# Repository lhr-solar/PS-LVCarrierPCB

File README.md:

# PS-LVCarrierPCB
One Big Beautiful Board

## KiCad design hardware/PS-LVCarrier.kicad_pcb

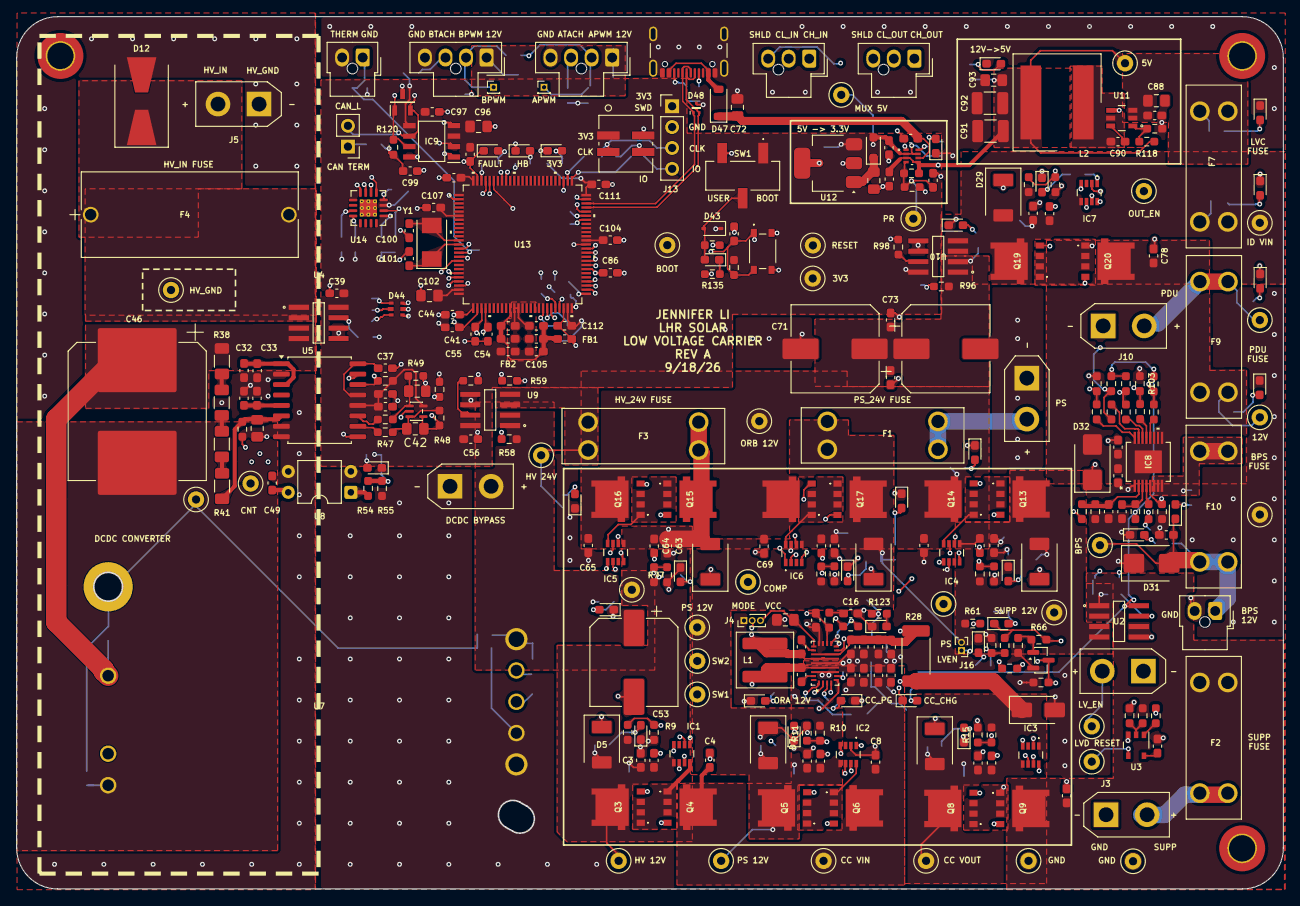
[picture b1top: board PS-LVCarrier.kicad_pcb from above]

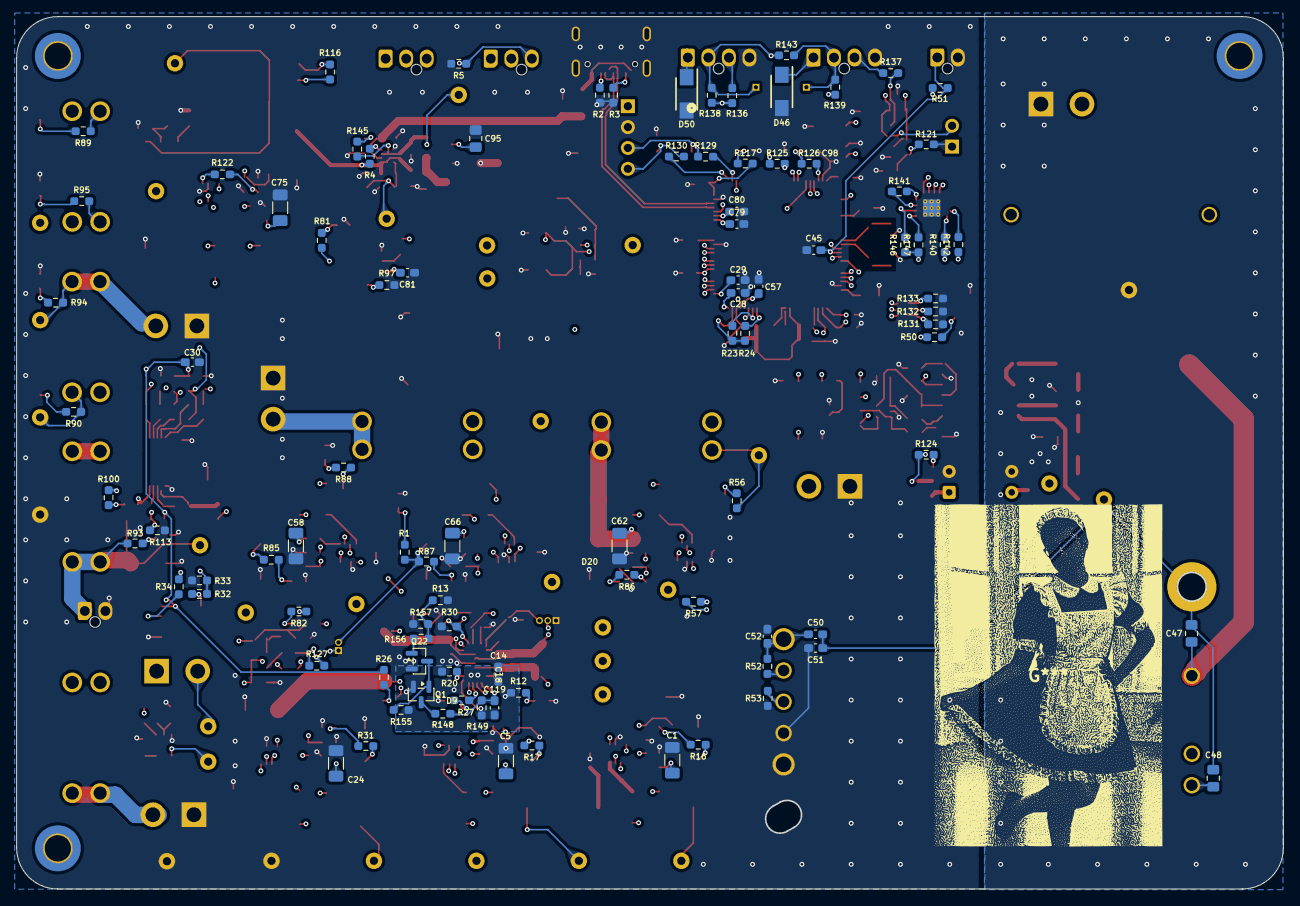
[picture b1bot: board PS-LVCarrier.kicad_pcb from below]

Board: 4 copper layers, 154.2 x 106.2 mm, 414 parts (95 on the bottom side), 209 nets.

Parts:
C1, C5, C24, C58, C62, C66, C75: 47u; C_1206_3216Metric_Pad1.33x1.80mm_HandSolder
C2, C4, C6, C8, C25, C27, C33, C35, C40, C59, C61, C63, C65, C67, C69, C76, C78, C85, C108, C110: 1u; C_0603_1608Metric_Pad1.08x0.95mm_HandSolder
C3, C7, C14, C18, C19, C26, C30, C39, C49, C56, C60, C64, C68, C77, C81, C97, C98, C99, C103, C104, C105, C106, C107, C109, C111, C112, C113, C114, C115, C116, C117, C119: 0.1u; C_0603_1608Metric_Pad1.08x0.95mm_HandSolder
C10, C11, C12, C13, C20, C21, C22, C23, C73, C74: 22u; C_0603_1608Metric_Pad1.08x0.95mm_HandSolder
C15, C31: 10n; C_0603_1608Metric_Pad1.08x0.95mm_HandSolder
C16: 4.7n; C_0603_1608Metric_Pad1.08x0.95mm_HandSolder
C17, C88: 4.7u; C_0805_2012Metric_Pad1.18x1.45mm_HandSolder
C28, C37, C45, C54, C57, C79, C83, C89, C90: 100n; C_0603_1608Metric_Pad1.08x0.95mm_HandSolder
C29, C41, C44, C55, C80, C86: 47n; C_0603_1608Metric_Pad1.08x0.95mm_HandSolder
C32, C34, C38, C84: 1n; C_0603_1608Metric_Pad1.08x0.95mm_HandSolder
C36: 1n; C_0805_2012Metric_Pad1.18x1.45mm_HandSolder
C42, C43: 1000p; C_0805_2012Metric_Pad1.18x1.45mm_HandSolder
C46: 100u; CP_Elec_16x22
C47, C48: 4700p; C_0805_2012Metric_Pad1.18x1.45mm_HandSolder
C50, C51: 0.022u; C_0603_1608Metric_Pad1.08x0.95mm_HandSolder
C52: 2.2u; C_0603_1608Metric_Pad1.08x0.95mm_HandSolder
C53: 680u; CP_Elec_10x10.5
C70, C71: 1000u; CP_Elec_10x12.5
C72, C94, C95, C96, C102: 10u; C_0805_2012Metric_Pad1.18x1.45mm_HandSolder
C82: 470n; C_0603_1608Metric_Pad1.08x0.95mm_HandSolder
C87: 2.2n; C_0603_1608Metric_Pad1.08x0.95mm_HandSolder
C91, C92: 22u; C_1210_3225Metric_Pad1.33x2.70mm_HandSolder
C93: 3.3u; C_0805_2012Metric_Pad1.18x1.45mm_HandSolder
C100, C101: 26p; C_0603_1608Metric_Pad1.08x0.95mm_HandSolder
D1: PS_LED; LED_0603_1608Metric_Pad1.05x0.95mm_HandSolder
D2: ORA_OUT_LED; LED_0603_1608Metric_Pad1.05x0.95mm_HandSolder
D3: D_Zener; D_SMA
D4, D6, D10, D17, D19, D21, D28: ORB_IN; LED_0603_1608Metric_Pad1.05x0.95mm_HandSolder
D5, D7, D11, D18, D20, D22, D29: SMBJ33D; SMBJ15DM3
D8, D9, D30, D45: LED; LED_0603_1608Metric_Pad1.05x0.95mm_HandSolder
D12: SMLJ150A; D_SMB-SMC_Universal_Handsoldering
D13, D14: HV24V_LED; LED_0603_1608Metric_Pad1.05x0.95mm_HandSolder
D15: DIODE_VOUT_LED; LED_0603_1608Metric_Pad1.05x0.95mm_HandSolder
D16: DISABLE_LED; LED_0603_1608Metric_Pad1.05x0.95mm_HandSolder
D23, D24: 12V_IN; LED_0603_1608Metric_Pad1.05x0.95mm_HandSolder
D25: HSS_IN; LED_0603_1608Metric_Pad1.05x0.95mm_HandSolder
D26: BPS_IN_LED; LED_0603_1608Metric_Pad1.05x0.95mm_HandSolder
D27: PDU_IN_LED; LED_0603_1608Metric_Pad1.05x0.95mm_HandSolder
D31, D32: D_TVS; D_SMB
D33, D49: 5V_LED; LED_0603_1608Metric_Pad1.05x0.95mm_HandSolder
D34: 3V3_LED; LED_0603_1608Metric_Pad1.05x0.95mm_HandSolder
D35: SBA130CH-AU_R1_000A1; D_SOD-323_HandSoldering
D36: CDSOT23-T24CAN
D37, D38: CHARGE_EN; LED_0603_1608Metric_Pad1.05x0.95mm_HandSolder
D39: DCDC_EN; LED_0603_1608Metric_Pad1.05x0.95mm_HandSolder
D40: HB_LED; LED_0603_1608Metric_Pad1.05x0.95mm_HandSolder
D41: FAULT_LED; LED_0603_1608Metric_Pad1.05x0.95mm_HandSolder
D42: LV_EN; LED_0603_1608Metric_Pad1.05x0.95mm_HandSolder
D43: TVS; D_SOD-323
D44: RGB_LED
D46, D50: VSSAF522-M3/H; SODFL5026X125N
D47: D_Schottky; D_SOD-123
D48: TPD2EUSB30DRTR
F1, F2, F3, F7, F9: TBD; Fuse-3557-2
F4: HV; HV-Fuse
F10: 5A; Fuse-3557-2
FB1, FB2: FerriteBead; C_0603_1608Metric_Pad1.08x0.95mm_HandSolder
H1, H2, H3: MountingHole; MountingHole_3.2mm_M3_DIN965_Pad_TopBottom
IC1, IC2, IC3, IC4, IC5, IC6, IC7: AP74502HQTA8-7; AP74502HQTA87
IC8: TPS2HCS08AQPWPRQ1
IC9: TCAN3413DR
J1: PS; AMASS_XT30UPB-M_1x02_P5.0mm_Vertical
J2: LV_ENABLE; AMASS_XT30UPB-M_1x02_P5.0mm_Vertical
J3: SUPP; AMASS_XT30UPB-M_1x02_P5.0mm_Vertical
J4: PWM/PFM; PinHeader_1x03_P1.00mm_Vertical
J5, J6: HV_IN; AMASS_XT30UPB-M_1x02_P5.0mm_Vertical
J8: HV_THERM; Molex_Nano-Fit_105309-xx02_1x02_P2.50mm_Vertical
J9: BPS_12V; Molex_Nano-Fit_105309-xx02_1x02_P2.50mm_Vertical
J10: PDU_12V; AMASS_XT30UPB-M_1x02_P5.0mm_Vertical
J11: CAN_IN; Molex_Nano-Fit_105309-xx03_1x03_P2.50mm_Vertical
J12: SWD_Header; SWD_Conn
J13: SWD; PinHeader_1x04_P2.54mm_Vertical
J14: FAN2; Molex_Nano-Fit_105309-xx04_1x04_P2.50mm_Vertical
J15: FAN1; Molex_Nano-Fit_105309-xx04_1x04_P2.50mm_Vertical
J16: in the off chance no supp pwr; PinHeader_1x02_P1.00mm_Vertical
J17: USB_C_Receptacle_USB2.0_16P; USB_C_Receptacle_GCT_USB4105-xx-A_16P_TopMnt_Horizontal
J18: CAN_OUT; Molex_Nano-Fit_105309-xx03_1x03_P2.50mm_Vertical
JP1: TRM; PinHeader_1x02_P2.54mm_Vertical
L1: 6.8u; L_Coilcraft_XAL6020-XXX
L2: 8.2u; 74439369082
Q1: BSS84; SOT-23
Q3, Q4, Q5, Q6, Q8, Q9, Q13, Q14, Q15, Q16, Q17, Q18, Q19, Q20: NVMFWS1D7N04XMT1G; NVMFWS3D0P04M8LT1G
Q10: IRLML0030; SOT-23
Q22: 2N7002; SOT-23
R1, R4, R9, R11, R12, R15, R16, R17, R31, R32, R42, R46, R47, R48, R49, R51, R56, R57, R58, R76, R78, R80, R81, R84, R85, R86, R87, R88, R89, R90, R92, R93, R95, R96, R102, R103, R106, R107, R108, R111, R112, R113, R128, R134, R136, R137, R138, R139, R140, R146, R147: 10k; R_0603_1608Metric_Pad0.98x0.95mm_HandSolder
R2, R3: 5.1k; R_0603_1608Metric_Pad0.98x0.95mm_HandSolder
R5, R52, R53, R143: 0; R_0603_1608Metric_Pad0.98x0.95mm_HandSolder
R8, R10, R14, R75, R77, R79, R91: 118k; R_0603_1608Metric_Pad0.98x0.95mm_HandSolder
R13, R23, R24, R29, R36, R55, R67, R118, R155, R157: 100k; R_0603_1608Metric_Pad0.98x0.95mm_HandSolder
R20: 49.9k; R_0603_1608Metric_Pad0.98x0.95mm_HandSolder
R25: 30k; R_0603_1608Metric_Pad0.98x0.95mm_HandSolder
R26, R27, R116, R117, R122, R123, R124, R125, R126, R127, R145: 1.3k; R_0603_1608Metric_Pad0.98x0.95mm_HandSolder
R28: 25m; R_2512_6332Metric_Pad1.40x3.35mm_HandSolder
R30: 8.66k; R_0603_1608Metric_Pad0.98x0.95mm_HandSolder
R33, R59, R66, R97, R131, R132, R133, R135, R156: 1k; R_0603_1608Metric_Pad0.98x0.95mm_HandSolder
R34, R45, R50, R60, R72, R98, R100, R110, R114: 4.7k; R_0603_1608Metric_Pad0.98x0.95mm_HandSolder
R35, R148: 200k; R_0603_1608Metric_Pad0.98x0.95mm_HandSolder
R37: 470k; R_0603_1608Metric_Pad0.98x0.95mm_HandSolder
R38, R39, R40, R41: 402k; R_1206_3216Metric_Pad1.30x1.75mm_HandSolder
R44, R61, R144: 47k; R_0603_1608Metric_Pad0.98x0.95mm_HandSolder
R54: 330; R_0603_1608Metric_Pad0.98x0.95mm_HandSolder
R68, R94, R142: 22k; R_0603_1608Metric_Pad0.98x0.95mm_HandSolder
R71: 16k; R_0603_1608Metric_Pad0.98x0.95mm_HandSolder
R82: 4.3k; R_0603_1608Metric_Pad0.98x0.95mm_HandSolder
R83, R141: 33k; R_0603_1608Metric_Pad0.98x0.95mm_HandSolder
R99, R104, R105, R129, R130: 22; R_0603_1608Metric_Pad0.98x0.95mm_HandSolder
R101: 10; R_0603_1608Metric_Pad0.98x0.95mm_HandSolder
R109: 220; R_0603_1608Metric_Pad0.98x0.95mm_HandSolder
R115: 470; R_0603_1608Metric_Pad0.98x0.95mm_HandSolder
R119: 19.1k; R_0603_1608Metric_Pad0.98x0.95mm_HandSolder
R120, R121: 60; R_0603_1608Metric_Pad0.98x0.95mm_HandSolder
R149: 26.1k; R_0603_1608Metric_Pad0.98x0.95mm_HandSolder
Reset1: Reset; TL3365AF180QG
SW1: SW_SPDT; BootSW
TP2: ORA_OUT_TP; TestPoint_Loop_D2.50mm_Drill1.0mm_LowProfile
TP3, TP4, TP9, TP30, TP31, TP32, TP39: DIODE_VIN; TestPoint_Loop_D2.50mm_Drill1.0mm_LowProfile
TP6: COMP; TestPoint_Loop_D2.50mm_Drill1.0mm_LowProfile
TP7: SW1; TestPoint_Loop_D2.50mm_Drill1.0mm_LowProfile
TP8: SW2; TestPoint_Loop_D2.50mm_Drill1.0mm_LowProfile
TP12: LVD_RESET; TestPoint_Loop_D2.50mm_Drill1.0mm_LowProfile
TP13: HV_GND; TestPoint_Loop_D2.50mm_Drill1.0mm_LowProfile
TP14, TP15, TP16: LV_GND; TestPoint_Loop_D2.50mm_Drill1.0mm_LowProfile
TP19: CNT; TestPoint_Loop_D2.50mm_Drill1.0mm_LowProfile
TP20: HV_24V_OUT; TestPoint_Loop_D2.50mm_Drill1.0mm_LowProfile
TP21: Earf; TestPoint_Loop_D2.50mm_Drill1.0mm_LowProfile
TP25: LV_EN_TP; TestPoint_Loop_D2.50mm_Drill1.0mm_LowProfile
TP26: SUPP_DIODE_EN; TestPoint_Loop_D2.50mm_Drill1.0mm_LowProfile
TP29: DIODE_VOUT; TestPoint_Loop_D2.50mm_Drill1.0mm_LowProfile
TP33: BOOT; TestPoint_Loop_D2.50mm_Drill1.0mm_LowProfile
TP34: RESET; TestPoint_Loop_D2.50mm_Drill1.0mm_LowProfile
TP35: OUTPUT_EN; TestPoint_Loop_D2.50mm_Drill1.0mm_LowProfile
TP36: PR1; TestPoint_Loop_D2.50mm_Drill1.0mm_LowProfile
TP37: BPS_IN_TP; TestPoint_Loop_D2.50mm_Drill1.0mm_LowProfile
TP38: PDU_IN_TP; TestPoint_Loop_D2.50mm_Drill1.0mm_LowProfile
TP42: HSS_VBB; TestPoint_Loop_D2.50mm_Drill1.0mm_LowProfile
TP43: Buck_5V; TestPoint_Loop_D2.50mm_Drill1.0mm_LowProfile
TP44: 3V3; TestPoint_Loop_D2.50mm_Drill1.0mm_LowProfile
TP45: MUX_5V; TestPoint_Loop_D2.50mm_Drill1.0mm_LowProfile
TP51: FAN_A_PWM; PinHeader_1x01_P1.00mm_Vertical
TP52: FAN_B_PWM; PinHeader_1x01_P1.00mm_Vertical
U1: TPS552872RYQR; TPS552872
U2, U9, U10: TMCS1107A2UQDR; TMCS1107A3BQDR
U3: TPS3840DL30DBVR; TPS3840DL33DBVR
U4: TMCS1107A3BQDR
U5: AMC3330; SOIC-16W_7.5x10.3mm_P1.27mm
U6: TLV6001DCK; SOT-353_SC-70-5
U7: CN150B110-12; lvc_dcdc
U8: LTV-817; DIP-4_W7.62mm
U11: LMR51635XDDCR; DDC0006A-MFG
U12: MCP1826S; SOT-223-3_TabPin2
U13: STM32G473VETx; 100PinMCU
U14: EMC2305-x-AP; Texas_RGV0016A_VQFN-16-1EP_4x4mm_P0.65mm_EP2.1x2.1mm_Therma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
U15: TPS2117DRLR
Y1: Crystal; Crystal_SMD_Abracon_ABM3-2Pin_5.0x3.2mm

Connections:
+3V3: C30.2, C38.1, C39.2, C40.1, C56.2, C81.2, C95.2, C96.1, C97.1, C98.1, C102.1, C104.1, C107.1, C109.1, C111.1, C112.1, FB2.1, IC9.3 (VCC), IC9.5 (SHDNV_IO), J12.1, J13.1, R23.1, R24.1, R26.1, R44.1, R51.1, R101.1, R102.1, R110.1, R111.2, R117.1, R128.2, R136.2, R137.2, R138.1, R139.1, R140.1, R141.1, R142.1, R146.1, R147.1, SW1.1 (A), TP44.1 (1_1), U2.8 (VS), U4.8 (VS), U5.12 (VDD), U6.5 (V+), U9.8 (VS), U10.8 (VS), U12.3 (VO), U13.6 (VBAT), U13.24 (VDD), U13.49 (VDD), U13.64 (VDD), U13.75 (VDD), U13.100 (VDD), U14.3 (VDD)
+12V: D46.1 (K), D50.1 (K), J14.1, J15.1
/CAN/CAN_RX: IC9.4 (RXD), U13.92 (PB5)
/CAN/CAN_TX: IC9.1 (TXD), U13.93 (PB6)
/CAN_H: D36.1 (CAN_H), IC9.7 (CANH), J11.1 (CAN_H), J18.1 (CAN_H), R120.1
/CAN_L: D36.2 (CAN_L), IC9.6 (CANL), J11.2 (CAN_L), J18.2 (CAN_L), JP1.2 (B)
/CHARGE_EN: R13.1, R123.1, R156.1, R157.2, U13.45 (PE14)
/CHG_CC: D8.1 (K), R23.2, U1.4 (*CC), U13.44 (PE13)
/CHG_PG: R24.2, R27.1, U1.3 (PG), U13.43 (PE12)
/DI_MODE: R108.1, R113.2, U13.58 (PD11)
/Fans/ADDR_SEL: R141.2, U14.4 (ADDR_SEL)
/Fans/FAN_ALERT: R140.2, U13.2 (PE3), U14.12 (~ALERT)
/Fans/FAN_A_PWM: J15.2, R138.2, R143.1, TP51.1 (1_1), U14.5 (PWM1)
/Fans/FAN_A_TACH: J15.3, R136.1, U14.6 (TACH1)
/Fans/FAN_B_PWM: J14.2, R139.2, R143.2, TP52.1 (1_1), U14.7 (PWM2)
/Fans/FAN_B_TACH: J14.3, R137.1, U14.8 (TACH2)
/Fans/FAN_CLK: R142.2, U14.11 (CLK)
/Fans/I2C_SCL: R146.2, U13.78 (PA15), U14.2 (SMCLK)
/Fans/I2C_SDA: R147.2, U13.96 (PB9), U14.1 (SMDATA)
/HSS_FLT_WK: R110.2, R112.2, U13.61 (PD14)
/HSS_MOSI: R99.1, R103.2, U13.54 (PB15)
/HSS_SCLK: R105.1, R106.2, U13.52 (PB13)
/HSS_SNS: C86.2, R114.2, U13.57 (PD10)
/HSS_SPI_CS: R102.2, R104.1, U13.62 (PD15)
/HV Input/HV -> 12V/CNT: C49.1, TP19.1 (1_1), U7.2 (CNT), U8.4
/HV Input/HV -> 12V/HV_24V_OUT: F3.1, R56.1, TP20.1 (1_1), U9.3 (IN-), U9.4 (IN-)
/HV Input/HV -> 12V/HV_IN: C46.1, C47.1, R38.1, U4.3 (IN-), U4.4 (IN-), U7.1 (IN+)
/HV Input/HV -> 12V/OUT+: C50.1, C52.1, C53.1, J6.2, R52.2, R57.1, R58.1, U7.9 (OUT+), U9.1 (IN+), U9.2 (IN+)
/HV Input/HV Input/DCDC_OUT: C32.1, C33.1, U5.1 (DCDC_OUT), U5.3 (HLDO_IN)
/HV Input/HV Input/HLDO_OUT: C34.1, C35.1, U5.5 (HLDO_OUT)
/HV Input/HV Input/HV_ISNS: R50.1, U4.7 (VOUT)
/HV Input/HV Input/HV_VSNS: C42.1, R45.1, R48.2, U6.4
/HV Input/HV Input/HV_VSNS+: R46.1, U5.11 (OUTP)
/HV Input/HV Input/HV_VSNS-: R47.2, U5.10 (OUTN)
/HV Input/HV Input/IN+: C36.2, R41.2, R42.1, U5.6 (INP)
/HV Input/HV Input/LDO_OUT: C37.1, U5.13 (LDO_OUT), U5.16 (DCDC_IN)
/HV Input/HV_12V_FUSED: C1.1, C2.1, C3.1, C62.1, C63.1, C64.1, D5.2 (A), D20.2 (A), F3.2, IC1.5 (VIN), IC5.5 (VIN), Q3.5, Q3.6, Q3.7, Q3.8, Q3.9, Q15.5, Q15.6, Q15.7, Q15.8, Q15.9, R8.1, R16.1, R77.1, R86.1, TP3.1 (1_1), TP31.1 (1_1)
/HV_DCDC_EN: R54.2, R55.1, R124.1, U13.17 (PC2)
/HV_DCDC_TEMP: C45.2, J8.1, R51.2, U13.15 (PC0)
/HV_IN_I: C44.1, R50.2, U13.26 (PA4)
/HV_IN_V: C41.1, R45.2, U13.27 (PA5)
/HV_IN_VFAULT: R44.2, U5.14 (DIAG), U13.16 (PC1)
/HV_OUT_I: C55.1, R60.2, U13.28 (PA6)
/HV_OUT_V: C54.1, R58.2, R59.1, U13.29 (PA7)
/LIMP_HOME: IC8.5 (LHI), R107.2, U13.59 (PD12)
/LVD_RESET: TP12.1 (1_1), U3.4 (MR_N), U13.47 (PB10)
/LV_EN_3V3: C57.1, R83.2, R84.2, R127.1, U13.46 (PE15)
/LV_I: C80.1, R98.2, U13.70 (PA9)
/LV_V: C79.1, R96.2, R97.1, U13.69 (PA8)
/MCU/FAULT: R126.1, U13.98 (PE1)
/MCU/HEARTBEAT: R125.1, U13.97 (PE0)
/MCU/STM32G473VETx/BOOT0: R134.1, TP33.1 (1_1), U13.95 (PB8-BOOT0)
/MCU/STM32G473VETx/GNDA: C103.2, C105.2, C108.2, C110.2, C113.2, FB1.1, U13.35 (VSSA)
/MCU/STM32G473VETx/NRST: C106.1, R128.1, Reset1.1, TP34.1 (1_1), U13.14 (PG10-NRST)
/MCU/STM32G473VETx/PA0: D44.5, U13.20 (PA0-GPIO_BLUE)
/MCU/STM32G473VETx/PA1: D44.3, U13.21 (PA1-GPIO_RED)
/MCU/STM32G473VETx/PA2: D44.1, U13.22 (PA2-GPIO_GREEN)
/MCU/STM32G473VETx/SWCLK: R129.1, U13.77 (PA14)
/MCU/STM32G473VETx/SWDIO: R130.1, U13.76 (PA13)
/MCU/STM32G473VETx/VDDA: C103.1, C105.1, C108.1, C110.1, C113.1, FB2.2, U13.36 (VREF+), U13.37 (VDDA)
/MISO: R109.1, R111.1, U13.53 (PB14)
/Main Diode ORs/12V_FUSED: C61.1, C65.1, C69.1, C70.1, C71.1, C73.1, C74.1, Q14.5, Q14.6, Q14.7, Q14.8, Q14.9, Q16.5, Q16.6, Q16.7, Q16.8, Q16.9, Q18.5, Q18.6, Q18.7, Q18.8, Q18.9, R81.1, R88.1, R96.1, TP29.1 (1_1), U10.1 (IN+), U10.2 (IN+)
/Main Diode ORs/HV_OVLO: IC5.7 (OVLO), R77.2, R78.1
/Main Diode ORs/Ideal Diode1/GATE: IC4.6 (GATE), Q13.4, Q14.4
/Main Diode ORs/Ideal Diode1/SRC: IC4.8 (SRC), Q13.1, Q13.2, Q13.3, Q14.1, Q14.2, Q14.3
/Main Diode ORs/Ideal Diode2/GATE: IC5.6 (GATE), Q15.4, Q16.4
/Main Diode ORs/Ideal Diode2/SRC: IC5.8 (SRC), Q15.1, Q15.2, Q15.3, Q16.1, Q16.2, Q16.3
/Main Diode ORs/Ideal Diode3/GATE: IC6.6 (GATE), Q17.4, Q18.4
/Main Diode ORs/Ideal Diode3/SRC: IC6.8 (SRC), Q17.1, Q17.2, Q17.3, Q18.1, Q18.2, Q18.3
/Main Diode ORs/PS_12V_FUSED: C5.1, C6.1, C7.1, C66.1, C67.1, C68.1, D7.2 (A), D22.2 (A), F1.2, IC2.5 (VIN), IC6.5 (VIN), J16.2, Q5.5, Q5.6, Q5.7, Q5.8, Q5.9, Q17.5, Q17.6, Q17.7, Q17.8, Q17.9, R1.1, R10.1, R17.1, R79.1, R87.1, TP4.1 (1_1), TP32.1 (1_1)
/Main Diode ORs/PS_OVLO: IC6.7 (OVLO), R79.2, R80.1
/Main Diode ORs/SUPP_12V_FUSED: C58.1, C59.1, C60.1, D18.2 (A), IC4.5 (VIN), Q13.5, Q13.6, Q13.7, Q13.8, Q13.9, R61.1, R75.1, R82.1, R85.1, TP30.1 (1_1), U2.3 (IN-), U2.4 (IN-)
/Main Diode ORs/SUPP_OVLO: IC4.7 (OVLO), R75.2, R76.1
/OUTPUT_EN: IC7.1 (EN/UVLO), R122.1, TP35.1 (1_1), U13.71 (PA10)
/Ouput/12V_OUT: C78.1, C84.1, C85.1, D32.2 (A2), F9.1, IC8.17 (VBB), Q20.5, Q20.6, Q20.7, Q20.8, Q20.9, R90.1, TP42.1 (1_1)
/Ouput/BPS_FUSED: C83.2, D30.1 (K), D31.2 (A2), F10.2, J9.1, R93.1, TP37.1 (1_1)
/Ouput/HSS/HSS_FLT_WAKE: IC8.12 (~FLT_/_~WAKE_SIG), R112.1
/Ouput/HSS/HSS_SPI_CS: IC8.15 (NCS), R104.2
/Ouput/HSS/MOSI: IC8.13 (SDI), R99.2
/Ouput/HSS/SCLK: IC8.16 (SCLK), R105.2
/Ouput/HSS/SNS: C87.2, IC8.2 (SNS), R114.1, R115.1
/Ouput/HSS/VDD: C82.1, IC8.3 (VDD), R101.2
/Ouput/HSS/VOUT1: F10.1, IC8.6 (VOUT1_1), IC8.7 (VOUT1_2), IC8.8 (VOUT1_3), R100.1
/Ouput/Ideal Diode/DIODE_VIN: C75.1, C76.1, C77.1, D29.2 (A), F7.2, IC7.5 (VIN), Q19.5, Q19.6, Q19.7, Q19.8, Q19.9, R91.1, R95.1, TP39.1 (1_1), U10.3 (IN-), U10.4 (IN-)
/Ouput/Ideal Diode/GATE: IC7.6 (GATE), Q19.4, Q20.4
/Ouput/Ideal Diode/OVLO: IC7.7 (OVLO), R91.2, R92.1
/Ouput/Ideal Diode/SRC: IC7.8 (SRC), Q19.1, Q19.2, Q19.3, Q20.1, Q20.2, Q20.3
/Ouput/LVC_12V_FUSED: C88.1, C89.1, F7.1, R89.1, U11.2 (EN), U11.3 (VIN)
/Ouput/PDU_FUSED: F9.2, J10.2, R94.1, TP38.1 (1_1)
/Power + Data/5V -> 3.3V LDO/Vin: C117.1, D35.2 (A), R145.1, TP45.1 (1_1), U15.2 (VOUT), U15.7 (VOUT__1)
/Power + Data/12V -> 5V Buck Converter/CB: C90.1, U11.6 (CB)
/Power + Data/12V -> 5V Buck Converter/FB: R118.2, R119.1, U11.1 (FB)
/Power + Data/12V -> 5V Buck Converter/SW: C90.2, L2.1, U11.5 (SW)
/Power + Data/12V -> 5V Buck Converter/V_out_5V: C91.1, C92.1, C93.1, C114.1, L2.2, R4.1, R71.1, R116.1, R118.1, TP43.1 (1_1), U15.3 (VIN1), U15.5 (MODE)
/Power + Data/Power Mux/PR1: C116.1, R71.2, R72.1, TP36.1 (1_1), U15.4 (PR1)
/Power + Data/USB/CC1: J17.A5 (CC1), R2.2
/Power + Data/USB/CC2: J17.B5 (CC2), R3.2
/Power + Data/USB/VBUS_IN: D47.2 (A), J17.A4 (VBUS), J17.A9 (VBUS), J17.B4 (VBUS), J17.B9 (VBUS)
/Power + Data/USB_5V: C72.2, C115.1, D47.1 (K), U15.6 (VIN2)
/SHIELD: J11.3 (SHIELD), J18.3 (SHIELD), R5.1
/SUPP_I: C29.1, R34.2, U13.51 (PB12)
/SUPP_V: C28.1, R32.2, R33.1, U13.50 (PB11)
/Supp Input/CC Buck/BOOT1: C18.1, U1.20 (BOOT1)
/Supp Input/CC Buck/BOOT2: C19.1, U1.19 (BOOT2)
/Supp Input/CC Buck/CC_VIN: C4.1, C8.1, C10.1, C11.1, C12.1, C13.1, C14.1, Q1.2 (S), Q4.5, Q4.6, Q4.7, Q4.8, Q4.9, Q6.5, Q6.6, Q6.7, Q6.8, Q6.9, R12.1, R155.1, TP2.1 (1_1), U1.7 (VIN)
/Supp Input/CC Buck/CC_VOUT: C24.1, C25.1, C26.1, D3.1 (K), D11.2 (A), IC3.1 (EN/UVLO), IC3.5 (VIN), Q8.5, Q8.6, Q8.7, Q8.8, Q8.9, R14.1, R28.1, R29.1, R31.1, TP9.1 (1_1), U1.13 (ISN)
/Supp Input/CC Buck/COMP: C15.1, R25.1, TP6.1 (1_1), U1.15 (COMP)
/Supp Input/CC Buck/EN/UVLO: C119.1, R148.2, R149.1, U1.1 (EN/UVLO)
/Supp Input/CC Buck/FB: R29.2, R30.1, U1.14 (FB)
/Supp Input/CC Buck/FSW: R20.1, U1.6 (FSW)
/Supp Input/CC Buck/MODE: J4.2, U1.2 (MODE)
/Supp Input/CC Buck/SW1: C18.2, L1.1, TP7.1 (1_1), U1.8 (SW1)
/Supp Input/CC Buck/SW2: C19.2, L1.2, TP8.1 (1_1), U1.10 (SW2)
/Supp Input/CC Buck/VCC: C17.1, J4.3, U1.18 (VCC)
/Supp Input/CC Buck/VOUT: C20.1, C21.1, C22.1, C23.1, R28.2, U1.11 (VOUT), U1.12 (ISP)
/Supp Input/CC_OVLO: IC3.7 (OVLO), R14.2, R15.1
/Supp Input/HV_OVLO: IC1.7 (OVLO), R8.2, R9.1
/Supp Input/Ideal Diode1/GATE: IC2.6 (GATE), Q5.4, Q6.4
/Supp Input/Ideal Diode1/SRC: IC2.8 (SRC), Q5.1, Q5.2, Q5.3, Q6.1, Q6.2, Q6.3
/Supp Input/Ideal Diode3/GATE: IC1.6 (GATE), Q3.4, Q4.4
/Supp Input/Ideal Diode3/SRC: IC1.8 (SRC), Q3.1, Q3.2, Q3.3, Q4.1, Q4.2, Q4.3
/Supp Input/Ideal Diode4/GATE: IC3.6 (GATE), Q8.4, Q9.4
/Supp Input/Ideal Diode4/SRC: IC3.8 (SRC), Q8.1, Q8.2, Q8.3, Q9.1, Q9.2, Q9.3
/Supp Input/LV_ENABLE: D16.1 (K), J2.2, R66.1, R83.1, TP25.1 (1_1)
/Supp Input/PS_OVLO: IC2.7 (OVLO), R10.2, R11.1
/Supp Input/SUPP_FUSED: C27.1, F2.2, Q9.5, Q9.6, Q9.7, Q9.8, Q9.9, R32.1, R35.1, U2.1 (IN+), U2.2 (IN+)
/USB_D+: D48.1 (D+), J17.A6 (D+), J17.B6 (D+), U13.73 (PA12)
/USB_D-: D48.2 (D-), J17.A7 (D-), J17.B7 (D-), U13.72 (PA11)
DIODE_EN: IC1.1 (EN/UVLO), IC2.1 (EN/UVLO), IC4.1 (EN/UVLO), IC5.1 (EN/UVLO), IC6.1 (EN/UVLO), Q10.3 (D), R37.1, R61.2, R68.1, R144.2, TP26.1 (1_1)
Earth: C47.2, C48.1, C50.2, C51.1, TP21.1 (1_1), U7.10 (PLATE)
HV_GND: C32.2, C33.2, C34.2, C35.2, C36.1, C49.2, D12.2 (A2), J5.1, R42.2, TP13.1 (1_1), U5.2 (DCDC_HGND), U5.7 (INN), U5.8 (HGND), U8.3
LV_GND: C1.2, C2.2, C4.2, C5.2, C6.2, C8.2, C10.2, C11.2, C12.2, C13.2, C14.2, C15.2, C16.2, C17.2, C20.2, C21.2, C22.2, C23.2, C24.2, C25.2, C27.2, C28.2, C29.2, C30.1, C31.2, C37.2, C38.2, C39.1, C40.2, C41.2, C43.2, C44.2, C45.1, C51.2, C52.2, C53.2, C54.2, C55.2, C56.1, C57.2, C58.2, C59.2, C61.2, C62.2, C63.2, C65.2, C66.2, C67.2, C69.2, C70.2, C71.2, C72.1, C73.2, C74.2, C75.2, C76.2, C78.2, C79.2, C80.2, C81.1, C82.2, C83.1, C84.2, C85.2, C86.1, C87.1, C88.2, C89.2, C91.2, C92.2, C93.2, C94.1, C95.1, C96.2, C97.2, C98.2, C99.1, C100.1, C101.1, C102.2, C104.2, C106.2, C107.2, C109.2, C111.2, C112.2, C114.2, C115.2, C116.2, C117.2, C119.2, D1.1 (K), D2.1 (K), D3.2 (A), D4.1 (K), D5.1 (K), D6.1 (K), D7.1 (K), D9.1 (K), D10.1 (K), D11.1 (K), D13.1 (K), D14.1 (K), D15.1 (K), D17.1 (K), D18.1 (K), D19.1 (K), D20.1 (K), D21.1 (K), D22.1 (K), D23.1 (K), D24.1 (K), D25.1 (K), D26.1 (K), D27.1 (K), D28.1 (K), D29.1 (K), D31.1 (A1), D32.1 (A1), D33.1 (K), D34.1 (K), D36.3 (GND), D37.1 (K), D38.1 (K), D39.1 (K), D40.1 (K), D41.1 (K), D42.1 (K), D43.1 (A1), D46.2 (A), D48.3 (GND), D49.1 (K), D50.2 (A), FB1.2, IC1.2 (GND), IC2.2 (GND), IC3.2 (GND), IC4.2 (GND), IC5.2 (GND), IC6.2 (GND), IC7.2 (GND), IC8.1 (GND), IC9.2 (GND), IC9.8 (STB), J1.1, J3.1, J4.1, J6.1, J8.2, J9.2, J10.1, J12.2, J13.2, J14.4, J15.4, J17.A1 (GND), J17.A12 (GND), J17.B1 (GND), J17.B12 (GND), J17.S1 (SHIELD), J17.S2 (Shield), J17.S3 (Shield), J17.S4 (Shield), Q10.2 (S), Q22.2 (S), R2.1, R3.1, R5.2, R9.2, R11.2, R13.2, R15.2, R20.2, R30.2, R33.2, R36.2, R49.1, R53.1, R55.2, R59.2, R67.2, R68.2, R72.2, R76.2, R78.2, R80.2, R84.1, R92.2, R97.2, R103.1, R106.1, R107.1, R113.1, R115.2, R119.2, R131.2, R132.2, R133.2, R135.2, R149.2, R157.1, Reset1.2, SW1.3 (C), TP14.1 (1_1), TP15.1 (1_1), TP16.1 (1_1), U1.5 (DITH/SYNC), U1.9 (PGND), U1.17 (AGND), U2.5 (GND), U2.6 (NC), U3.3 (GND), U4.5 (GND), U4.6 (NC), U5.9 (GND), U5.15 (DCDC_GND), U6.2 (V-), U7.5 (OUT-), U7.6 (SENSE-), U8.2, U9.5 (GND), U9.6 (NC), U10.5 (GND), U10.6 (NC), U11.4 (GND), U12.2 (GND), U13.23 (VSS), U13.48 (VSS), U13.63 (VSS), U13.74 (VSS), U13.99 (VSS), U14.17 (GND), U15.1 (GND)
unnamed: C16.1, R25.2
unnamed: C99.2, R120.2, R121.1
unnamed: D1.2 (A), R1.2
unnamed: D2.2 (A), R12.2
unnamed: D4.2 (A), R16.2
unnamed: D6.2 (A), R17.2
unnamed: D8.2 (A), R26.2
unnamed: D9.2 (A), R27.2
unnamed: D10.2 (A), R31.2
unnamed: D12.1 (A1), F4.1, J5.2
unnamed: D13.2 (A), R56.2
unnamed: D14.2 (A), R57.2
unnamed: D15.2 (A), R81.2
unnamed: D16.2 (A), R82.2
unnamed: D17.2 (A), R85.2
unnamed: D19.2 (A), R86.2
unnamed: D21.2 (A), R87.2
unnamed: D23.2 (A), R88.2
unnamed: D24.2 (A), R89.2
unnamed: D25.2 (A), R90.2
unnamed: D26.2 (A), R93.2
unnamed: D27.2 (A), R94.2
unnamed: D28.2 (A), R95.2
unnamed: D30.2 (A), R100.2
unnamed: D33.2 (A), R116.2
unnamed: D34.2 (A), R117.2
unnamed: C94.2, D35.1 (K), U12.1 (VI)
unnamed: D37.2 (A), R122.2
unnamed: D38.2 (A), R123.2
unnamed: D39.2 (A), R124.2
unnamed: D40.2 (A), R125.2
unnamed: D41.2 (A), R126.2
unnamed: D42.2 (A), R127.2
unnamed: D43.2 (A2), D45.2 (A), R134.2, SW1.2 (B)
unnamed: D44.2, R131.1
unnamed: D44.4, R132.1
unnamed: D44.6, R133.1
unnamed: D45.1 (K), R135.1
unnamed: D49.2 (A), R145.2
unnamed: F4.2, U4.1 (IN+), U4.2 (IN+)
unnamed: C3.2, IC1.4 (VCP)
unnamed: C7.2, IC2.4 (VCP)
unnamed: C26.2, IC3.4 (VCP)
unnamed: C60.2, IC4.4 (VCP)
unnamed: C64.2, IC5.4 (VCP)
unnamed: C68.2, IC6.4 (VCP)
unnamed: C77.2, IC7.4 (VCP)
unnamed: IC8.4 (DI), R108.2
unnamed: IC8.14 (SDO), R109.2
unnamed: F1.1, J1.2
unnamed: F2.1, J3.2
unnamed: J12.3, J13.3, R129.2
unnamed: J12.4, J13.4, R130.2
unnamed: J16.1, R144.1
unnamed: JP1.1 (A), R121.2
unnamed: Q1.3 (D), R148.1
unnamed: Q1.1 (G), Q22.3 (D), R155.2
unnamed: Q10.1 (G), R66.2, R67.1
unnamed: Q22.1 (G), R156.2
unnamed: R38.2, R39.1
unnamed: R39.2, R40.1
unnamed: R40.2, R41.1
unnamed: R54.1, U8.1
unnamed: R34.1, U2.7 (VOUT)
unnamed: C31.1, U3.5 (CT)
unnamed: R37.2, U3.1 (RESET_N)
unnamed: R35.2, R36.1, U3.2 (VDD)
unnamed: C43.1, R46.2, R49.2, U6.1 (+)
unnamed: C42.2, R47.1, R48.1, U6.3 (-)
unnamed: C46.2, C48.2, U7.4 (IN-)
unnamed: R52.1, U7.8 (SENSE+)
unnamed: R53.2, U7.7 (TRM)
unnamed: R60.1, U9.7 (VOUT)
unnamed: R98.1, U10.7 (VOUT)
unnamed: C100.2, U13.12 (PF0-OSC_IN), Y1.2
unnamed: C101.2, U13.13 (PF1-OSC_OUT), Y1.1
unnamed: R4.2, U15.8 (ST)

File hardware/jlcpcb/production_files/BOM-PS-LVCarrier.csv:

Comment,Designator,Footprint,LCSC,Quantity
0.022u,"C50,C51",C_0603_1608Metric_Pad1.08x0.95mm_HandSolder,C1697,2
0.1u,"C103,C104,C105,C106,C107,C109,C111,C112,C113,C114,C115,C116,C117,C119,C14,C18,C19,C26,C3,C30,C39,C49,C56,C60,C64,C68,C7,C77,C81,C97,C98,C99",C_0603_1608Metric_Pad1.08x0.95mm_HandSolder,C14663,32
1.3k,"R116,R117,R122,R123,R124,R125,R126,R127,R145,R26,R27",R_0603_1608Metric_Pad0.98x0.95mm_HandSolder,C22767,11
10,R101,R_0603_1608Metric_Pad0.98x0.95mm_HandSolder,C313648,1
1000p,"C42,C43",C_0805_2012Metric_Pad1.18x1.45mm_HandSolder,C1791,2
1000u,"C70,C71",CP_Elec_10x12.5,C22387800,2
100k,"R118,R13,R155,R157,R23,R24,R29,R36,R55,R67",R_0603_1608Metric_Pad0.98x0.95mm_HandSolder,C25803,10
100n,"C28,C37,C45,C54,C57,C79,C83,C89,C90",C_0603_1608Metric_Pad1.08x0.95mm_HandSolder,C14663,9
100u,C46,CP_Elec_16x22,C487536,1
10k,"R1,R102,R103,R106,R107,R108,R11,R111,R112,R113,R12,R128,R134,R136,R137,R138,R139,R140,R146,R147,R15,R16,R17,R31,R32,R4,R42,R46,R47,R48,R49,R51,R56,R57,R58,R76,R78,R80,R81,R84,R85,R86,R87,R88,R89,R9,R90,R92,R93,R95,R96",R_0603_1608Metric_Pad0.98x0.95mm_HandSolder,C25804,51
10u,"C102,C72,C94,C95,C96",C_0805_2012Metric_Pad1.18x1.45mm_HandSolder,C440198,5
118k,"R10,R14,R75,R77,R79,R8,R91",R_0603_1608Metric_Pad0.98x0.95mm_HandSolder,C25806,7
12V_IN,"D23,D24",LED_0603_1608Metric_Pad1.05x0.95mm_HandSolder,C7371904,2
16k,R71,R_0603_1608Metric_Pad0.98x0.95mm_HandSolder,C137788,1
19.1k,R119,R_0603_1608Metric_Pad0.98x0.95mm_HandSolder,C844132,1
1k,"R131,R132,R133,R135,R156,R33,R59,R66,R97",R_0603_1608Metric_Pad0.98x0.95mm_HandSolder,C21190,9
1n,C84,C_0603_1608Metric_Pad1.08x0.95mm_HandSolder,C100040,1
1n,"C32,C34,C38",C_0603_1608Metric_Pad1.08x0.95mm_HandSolder,C1588,3
1n,C36,C_0805_2012Metric_Pad1.18x1.45mm_HandSolder,C62774,1
1u,"C108,C110,C2,C25,C27,C33,C35,C4,C40,C59,C6,C61,C63,C65,C67,C69,C76,C78,C8,C85",C_0603_1608Metric_Pad1.08x0.95mm_HandSolder,C15849,20
2.2n,C87,C_0603_1608Metric_Pad1.08x0.95mm_HandSolder,C1604,1
2.2u,C52,C_0603_1608Metric_Pad1.08x0.95mm_HandSolder,C57895,1
200k,"R148,R35",R_0603_1608Metric_Pad0.98x0.95mm_HandSolder,C25811,2
22,"R104,R105,R129,R130,R99",R_0603_1608Metric_Pad0.98x0.95mm_HandSolder,C2930077,5
220,R109,R_0603_1608Metric_Pad0.98x0.95mm_HandSolder,C22356650,1
22k,"R142,R68,R94",R_0603_1608Metric_Pad0.98x0.95mm_HandSolder,C31850,3
22u,"C10,C11,C12,C13,C20,C21,C22,C23,C73,C74",C_0603_1608Metric_Pad1.08x0.95mm_HandSolder,C29519229,10
22u,"C91,C92",C_1210_3225Metric_Pad1.33x2.70mm_HandSolder,C778721,2
25m,R28,R_2512_6332Metric_Pad1.40x3.35mm_HandSolder,C105375,1
26.1k,R149,R_0603_1608Metric_Pad0.98x0.95mm_HandSolder,C103472,1
26p,"C100,C101",C_0603_1608Metric_Pad1.08x0.95mm_HandSolder,C92670,2
2N7002,Q22,SOT-23,C8545,1
3.3u,C93,C_0805_2012Metric_Pad1.18x1.45mm_HandSolder,C342775,1
30k,R25,R_0603_1608Metric_Pad0.98x0.95mm_HandSolder,C18681,1
330,R54,R_0603_1608Metric_Pad0.98x0.95mm_HandSolder,C49330142,1
33k,"R141,R83",R_0603_1608Metric_Pad0.98x0.95mm_HandSolder,C22356655,2
3V3_LED,D34,LED_0603_1608Metric_Pad1.05x0.95mm_HandSolder,C7371904,1
4.7k,"R100,R110,R114,R34,R45,R50,R60,R72,R98",R_0603_1608Metric_Pad0.98x0.95mm_HandSolder,C23162,9
4.7n,C16,C_0603_1608Metric_Pad1.08x0.95mm_HandSolder,C106218,1
4.7u,"C17,C88",C_0805_2012Metric_Pad1.18x1.45mm_HandSolder,C6962403,2
402k,"R38,R39,R40,R41",R_1206_3216Metric_Pad1.30x1.75mm_HandSolder,C25832,4
470,R115,R_0603_1608Metric_Pad0.98x0.95mm_HandSolder,C23179,1
4700p,"C47,C48",C_0805_2012Metric_Pad1.18x1.45mm_HandSolder,C1744,2
470k,R37,R_0603_1608Metric_Pad0.98x0.95mm_HandSolder,C23178,1
470n,C82,C_0603_1608Metric_Pad1.08x0.95mm_HandSolder,C1623,1
47k,"R144,R44,R61",R_0603_1608Metric_Pad0.98x0.95mm_HandSolder,C25819,3
47n,"C29,C41,C44,C55,C80,C86",C_0603_1608Metric_Pad1.08x0.95mm_HandSolder,C1622,6
49.9k,R20,R_0603_1608Metric_Pad0.98x0.95mm_HandSolder,C23184,1
5.1k,"R2,R3",R_0603_1608Metric_Pad0.98x0.95mm_HandSolder,C23186,2
5V_LED,"D33,D49",LED_0603_1608Metric_Pad1.05x0.95mm_HandSolder,C7371904,2
6.8u,L1,L_Coilcraft_XAL6020-XXX,C3911827,1
60,"R120,R121",R_0603_1608Metric_Pad0.98x0.95mm_HandSolder,C166918,2
680u,C53,CP_Elec_10x10.5,C2980167,1
8.66k,R30,R_0603_1608Metric_Pad0.98x0.95mm_HandSolder,C23114,1
AMC3330,U5,SOIC-16W_7.5x10.3mm_P1.27mm,C2999368,1
AP74502HQTA8-7,"IC1,IC2,IC3,IC4,IC5,IC6,IC7",AP74502HQTA87,C48989247,7
BPS_IN_LED,D26,LED_0603_1608Metric_Pad1.05x0.95mm_HandSolder,C7371904,1
BSS84,Q1,SOT-23,C114481,1
CDSOT23-T24CAN,D36,CDSOT23-T24CAN,C2959841,1
CHARGE_EN,"D37,D38",LED_0603_1608Metric_Pad1.05x0.95mm_HandSolder,C7371904,2
Crystal,Y1,Crystal_SMD_Abracon_ABM3-2Pin_5.0x3.2mm,C144380,1
DCDC_EN,D39,LED_0603_1608Metric_Pad1.05x0.95mm_HandSolder,C7371904,1
DIODE_VOUT_LED,D15,LED_0603_1608Metric_Pad1.05x0.95mm_HandSolder,C7371904,1
DISABLE_LED,D16,LED_0603_1608Metric_Pad1.05x0.95mm_HandSolder,C84263,1
D_Schottky,D47,D_SOD-123,C82544,1
D_TVS,"D31,D32",D_SMB,C428853,2
EMC2305-x-AP,U14,Texas_RGV0016A_VQFN-16-1EP_4x4mm_P0.65mm_EP2.1x2.1mm_ThermalVias,C621415,1
FAULT_LED,D41,LED_0603_1608Metric_Pad1.05x0.95mm_HandSolder,C84263,1
HB_LED,D40,LED_0603_1608Metric_Pad1.05x0.95mm_HandSolder,C7371904,1
HSS_IN,D25,LED_0603_1608Metric_Pad1.05x0.95mm_HandSolder,C7371904,1
HV24V_LED,"D13,D14",LED_0603_1608Metric_Pad1.05x0.95mm_HandSolder,C7371904,2
IRLML0030,Q10,SOT-23,C67272,1
LED,D45,LED_0603_1608Metric_Pad1.05x0.95mm_HandSolder,C125103,1
LED,"D8,D9",LED_0603_1608Metric_Pad1.05x0.95mm_HandSolder,C7371904,2
LED,D30,LED_0603_1608Metric_Pad1.05x0.95mm_HandSolder,C84263,1
LMR51635XDDCR,U11,DDC0006A-MFG,C42432812,1
LTV-817,U8,DIP-4_W7.62mm,C62715,1
LV_EN,D42,LED_0603_1608Metric_Pad1.05x0.95mm_HandSolder,C7371904,1
MCP1826S,U12,SOT-223-3_TabPin2,C126055,1
NVMFWS1D7N04XMT1G,"Q13,Q14,Q15,Q16,Q17,Q18,Q19,Q20,Q3,Q4,Q5,Q6,Q8,Q9",NVMFWS3D0P04M8LT1G,C133142,14
ORA_OUT_LED,D2,LED_0603_1608Metric_Pad1.05x0.95mm_HandSolder,C7371904,1
ORB_IN,"D10,D17,D19,D21,D28,D4,D6",LED_0603_1608Metric_Pad1.05x0.95mm_HandSolder,C7371904,7
PDU_IN_LED,D27,LED_0603_1608Metric_Pad1.05x0.95mm_HandSolder,C7371904,1
PS_LED,D1,LED_0603_1608Metric_Pad1.05x0.95mm_HandSolder,C7371904,1
RGB_LED,D44,RGB_LED,C264519,1
Reset,Reset1,TL3365AF180QG,C2886926,1
SBA130CH-AU_R1_000A1,D35,D_SOD-323_HandSoldering,C191023,1
SMBJ33D,"D11,D18,D20,D22,D29,D5,D7",SMBJ15DM3,C78419,7
STM32G473VETx,U13,100PinMCU,C730122,1
TCAN3413DR,IC9,TCAN3413DR,C22433320,1
TLV6001DCK,U6,SOT-353_SC-70-5,C2057455,1
TMCS1107A2UQDR,"U10,U2,U9",TMCS1107A3BQDR,C3684136,3
TMCS1107A3BQDR,U4,TMCS1107A3BQDR,C3684250,1
TPD2EUSB30DRTR,D48,TPD2EUSB30DRTR,C97502,1
TPS2117DRLR,U15,TPS2117DRLR,C22399676,1
TPS3840DL30DBVR,U3,TPS3840DL33DBVR,C2862542,1
TPS552872RYQR,U1,TPS552872,C22427496,1
TVS,D43,D_SOD-323,C725495,1
VSSAF522-M3/H,"D46,D50",SODFL5026X125N,C20039242,2
CN150B110-12,U7,lvc_dcdc,,1
TPS2HCS08AQPWPRQ1,IC8,TPS2HCS08AQPWPRQ1,,1
